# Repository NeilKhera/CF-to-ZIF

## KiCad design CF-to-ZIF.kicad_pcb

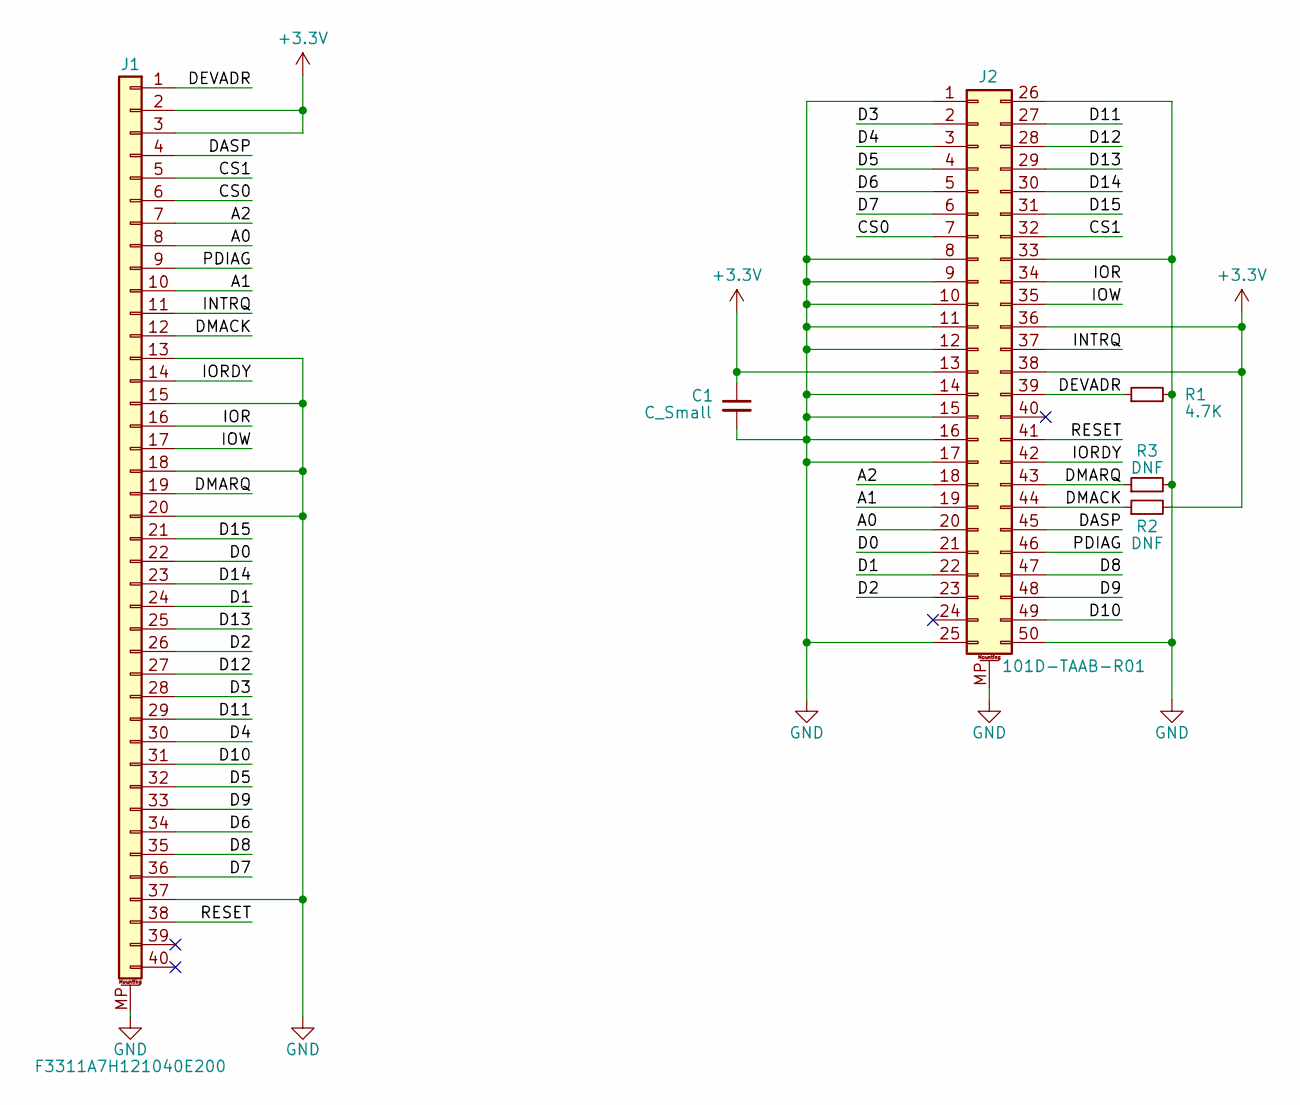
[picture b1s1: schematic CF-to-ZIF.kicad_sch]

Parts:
C1: C_Small; C_0805_2012Metric
J1: F3311A7H121040E200
J2: 101D-TAAB-R01
R1: 4.7K; R_0603_1608Metric
R2, R3: DNF; R_0603_1608Metric

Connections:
+3.3V: C1.1, J1.2, J1.3, J2.13, J2.36, J2.38, R2.2
/A0: J1.8, J2.20
/A1: J1.10, J2.19
/A2: J1.7, J2.18
/CS0: J1.6, J2.7
/CS1: J1.5, J2.32
/D0: J1.22, J2.21
/D1: J1.24, J2.22
/D2: J1.26, J2.23
/D3: J1.28, J2.2
/D4: J1.30, J2.3
/D5: J1.32, J2.4
/D6: J1.34, J2.5
/D7: J1.36, J2.6
/D8: J1.35, J2.47
/D9: J1.33, J2.48
/D10: J1.31, J2.49
/D11: J1.29, J2.27
/D12: J1.27, J2.28
/D13: J1.25, J2.29
/D14: J1.23, J2.30
/D15: J1.21, J2.31
/DASP: J1.4, J2.45
/DEVADR: J1.1, J2.39, R1.1
/DMACK: J1.12, J2.44, R2.1
/DMARQ: J1.19, J2.43, R3.1
/INTRQ: J1.11, J2.37
/IOR: J1.16, J2.34
/IORDY: J1.14, J2.42
/IOW: J1.17, J2.35
/PDIAG: J1.9, J2.46
/RESET: J1.38, J2.41
GND: C1.2, J1.13, J1.15, J1.18, J1.20, J1.37, J1.MP (MountPin), J2.1, J2.8, J2.9, J2.10, J2.11, J2.12, J2.14, J2.15, J2.16, J2.17, J2.25, J2.26, J2.33, J2.50, J2.MP (MountPin), R1.2, R3.2

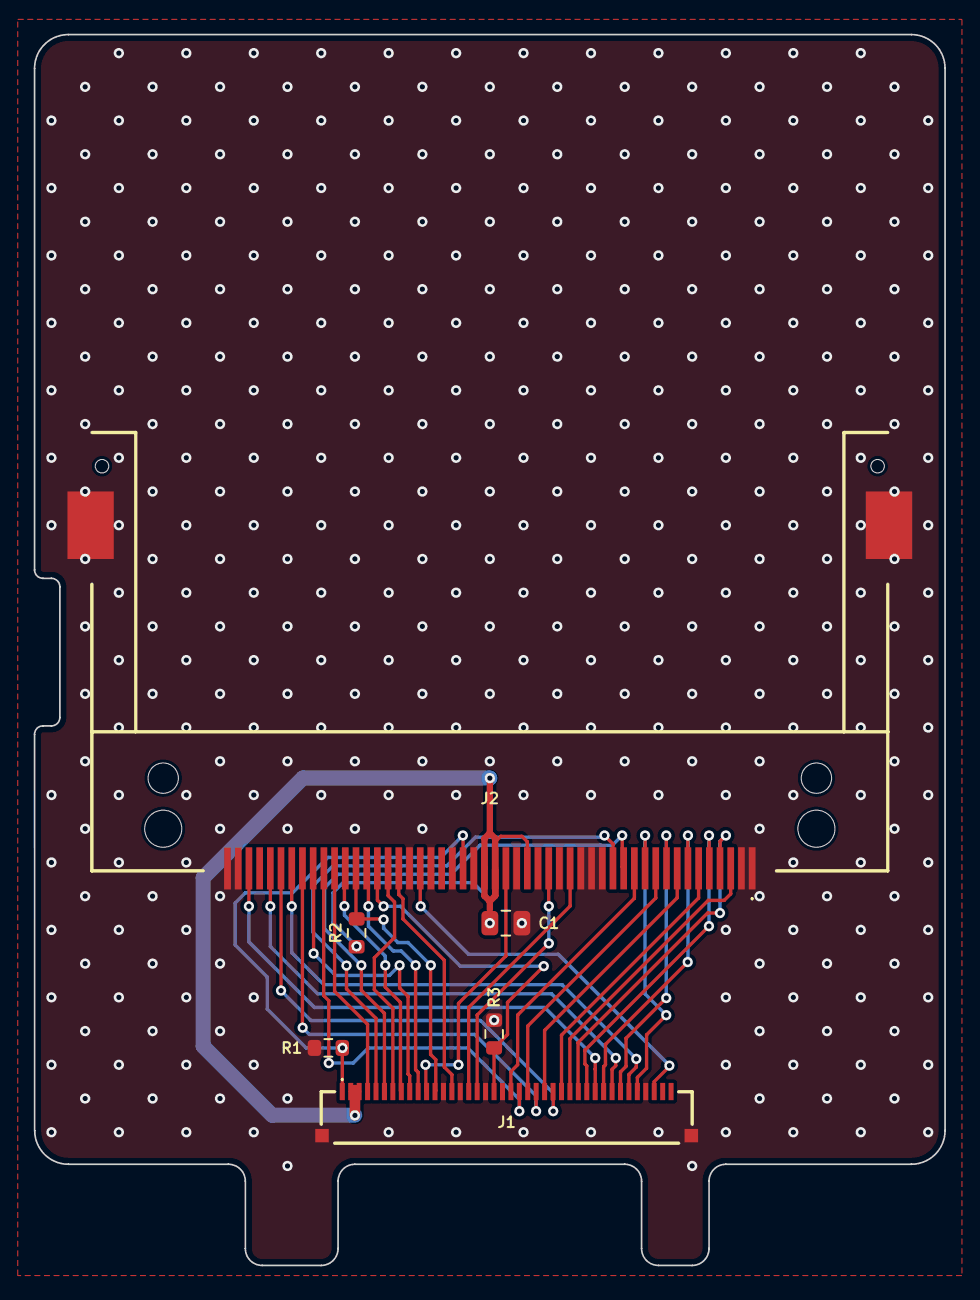
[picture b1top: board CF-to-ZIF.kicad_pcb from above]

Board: 2 copper layers, 54.0 x 73.0 mm, 6 parts (0 on the bottom side), 33 nets.

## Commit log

2024-05-03 Added .gitignore
2024-05-03 File upload
2024-05-03 Update to KiCad 8
